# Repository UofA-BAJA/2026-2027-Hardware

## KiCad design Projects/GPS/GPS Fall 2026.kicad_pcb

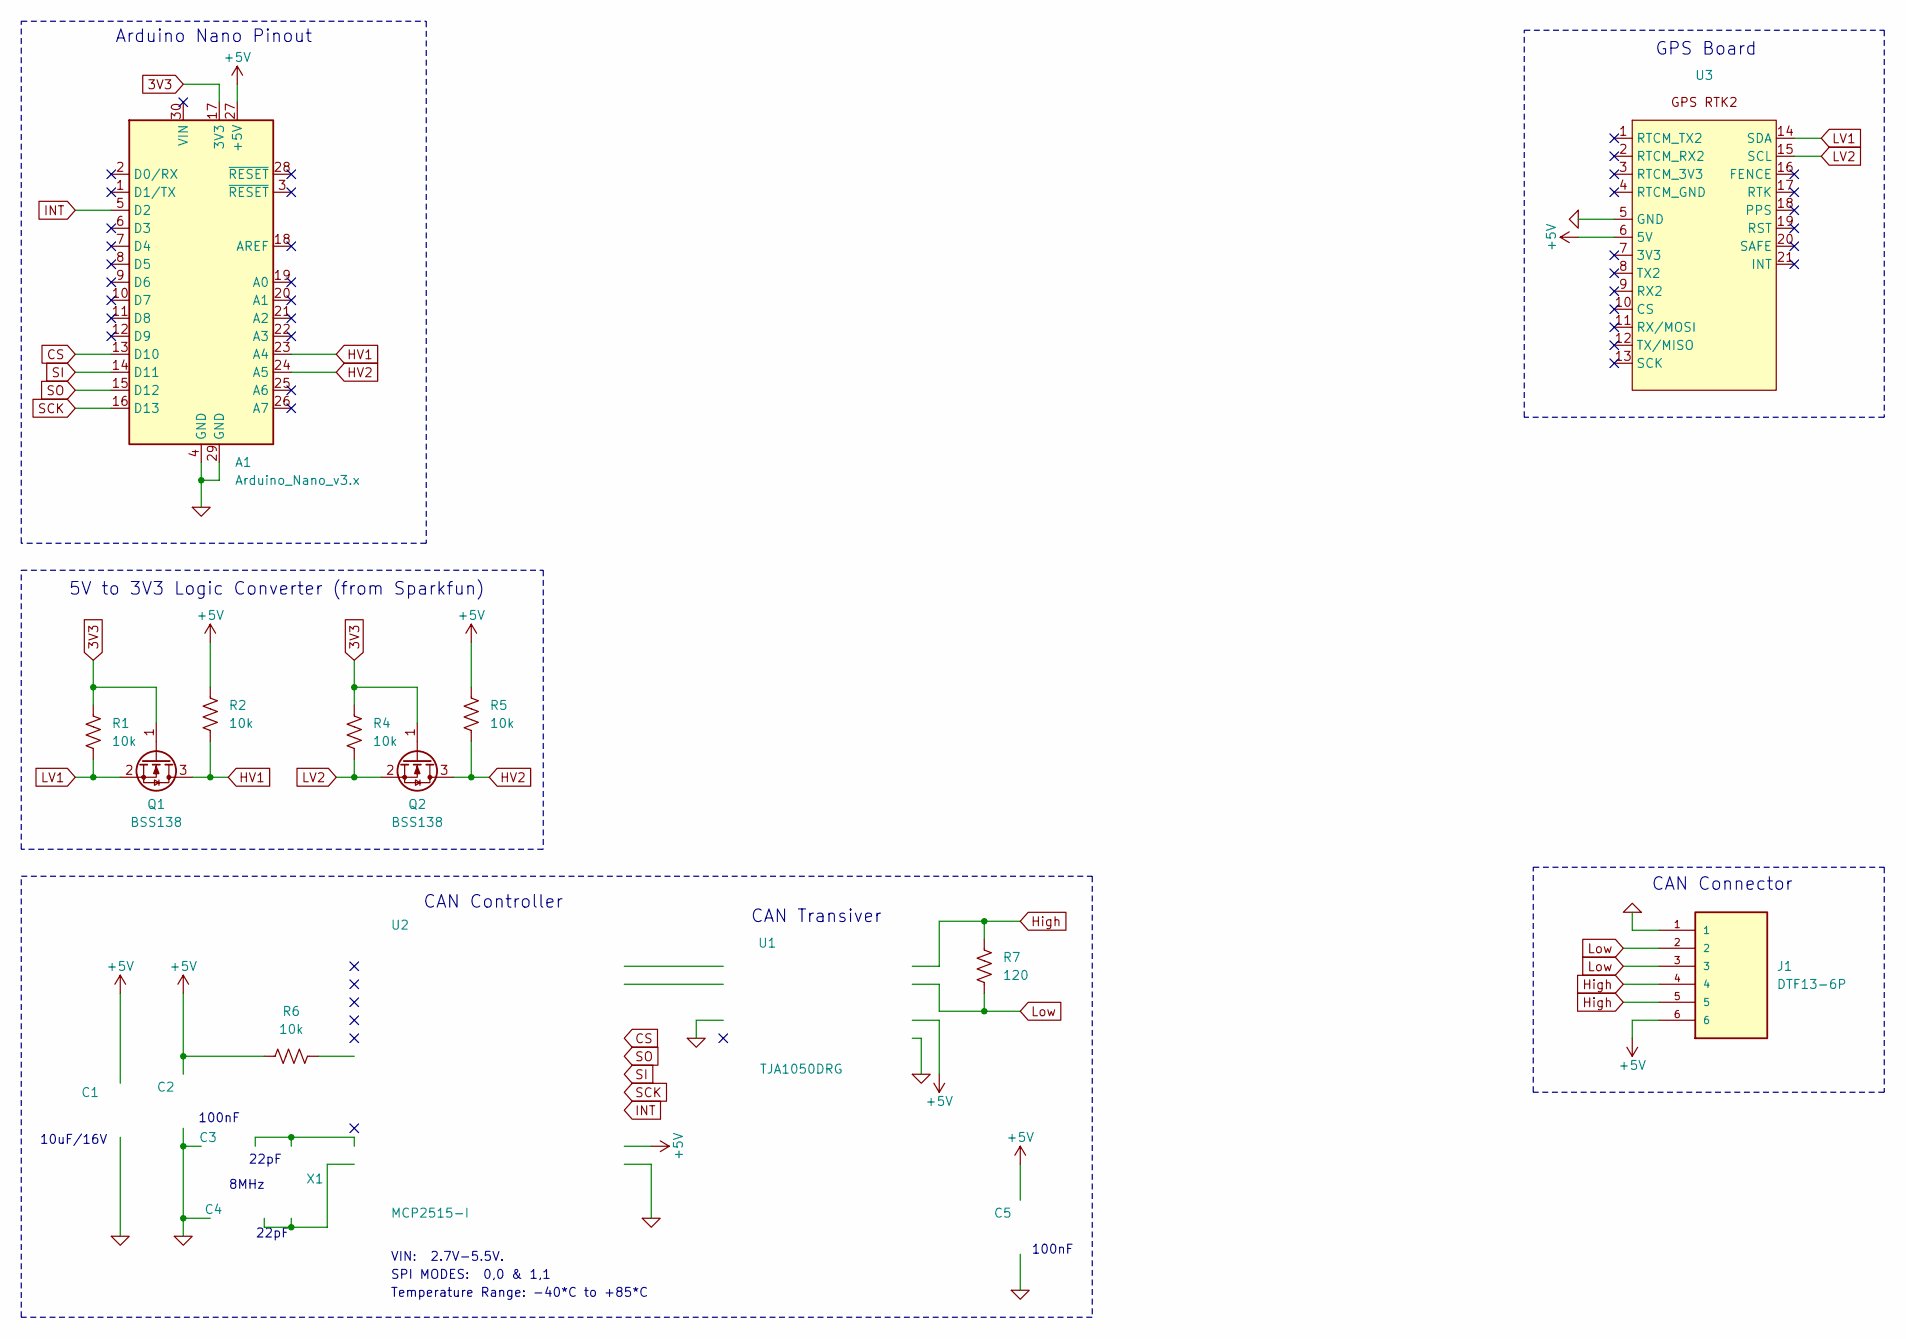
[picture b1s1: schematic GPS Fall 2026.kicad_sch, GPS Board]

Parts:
A1: Arduino_Nano_v3.x; Arduino_Nano
C1: 10uF/16V; CP_Radial_Tantal_D5.0mm_P2.50mm
C2, C5: 100nF; CP_Radial_D5.0mm_P2.50mm; PART NUMBER C0603-N.C.
C3, C4: 22pF; CP_Radial_D5.0mm_P2.50mm; PART NUMBER C0603-N.C.
J1: DTF13-6P; TE_DTF13-6P; PARTREV B
Q1, Q2: BSS138; SOT-23_Handsoldering
R1, R2, R4, R5, R6: 10k; R_Axial_DIN0207_L6.3mm_D2.5mm_P10.16mm_Horizontal
R7: 120; R_Axial_DIN0207_L6.3mm_D2.5mm_P10.16mm_Horizontal
U1: TJA1050DRG; SOIC-8_5.3x5.3mm_P1.27mm; MANUFACTURER PART TJA1050DRG; LCSC PART NAME TJA1050DRG
U2: MCP2515-I; SOIC-18W_7.5x11.6mm_P1.27mm; MANUFACTURER PART MCP2515-I; JLCPCB PART CLASS Extended Part
U3: GPS_RTK2
X1: 8MHz; Crystal_SMD_HC49-SD

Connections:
0: A1.4 (GND), A1.29 (GND), C1.2, C2.1, C3.2, C4.2, C5.1, J1.1, U1.2 (GND), U1.8 (STB), U2.9 (VSS), U3.5 (GND)
3V3: A1.17 (3V3), Q1.1 (G), Q2.1 (G), R1.1, R4.1
+5V: A1.27 (+5V), C1.1, C2.2, C5.2, J1.6, R2.1, R5.1, R6.1, U1.3 (VCC), U2.18 (VDD), U3.6 (5V)
CS: A1.13 (D10), U2.16 (~CS)
HV1: A1.23 (A4), Q1.3 (D), R2.2
HV2: A1.24 (A5), Q2.3 (D), R5.2
High: J1.4, J1.5, R7.1, U1.7 (CANH)
INT: A1.5 (D2), U2.12 (~INT)
LV1: Q1.2 (S), R1.2, U3.14 (SDA)
LV2: Q2.2 (S), R4.2, U3.15 (SCL)
Low: J1.2, J1.3, R7.2, U1.6 (CANL)
unnamed: U1.4 (RXD), U2.2 (RXCAN)
unnamed: U1.1 (TXD), U2.1 (TXCAN)
unnamed: C4.1, U2.8 (OSC1), X1.1
unnamed: C3.1, U2.7 (OSC2), X1.2
unnamed: R6.2, U2.17 (~RESET)
SCK: A1.16 (D13), U2.13 (SCK)
SI: A1.14 (D11), U2.14 (SI)
SO: A1.15 (D12), U2.15 (SO)

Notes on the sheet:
VIN: 2.7V-5.5V.
100nF
5V to 3V3 Logic Converter (from Sparkfun)
CAN Controller
CAN Connector
SPI MODES: 0,0 & 1,1
Arduino Nano Pinout
8MHz
GPS Board
CAN Transiver
22pF
Temperature Range: -40*C to +85*C
10uF/16V

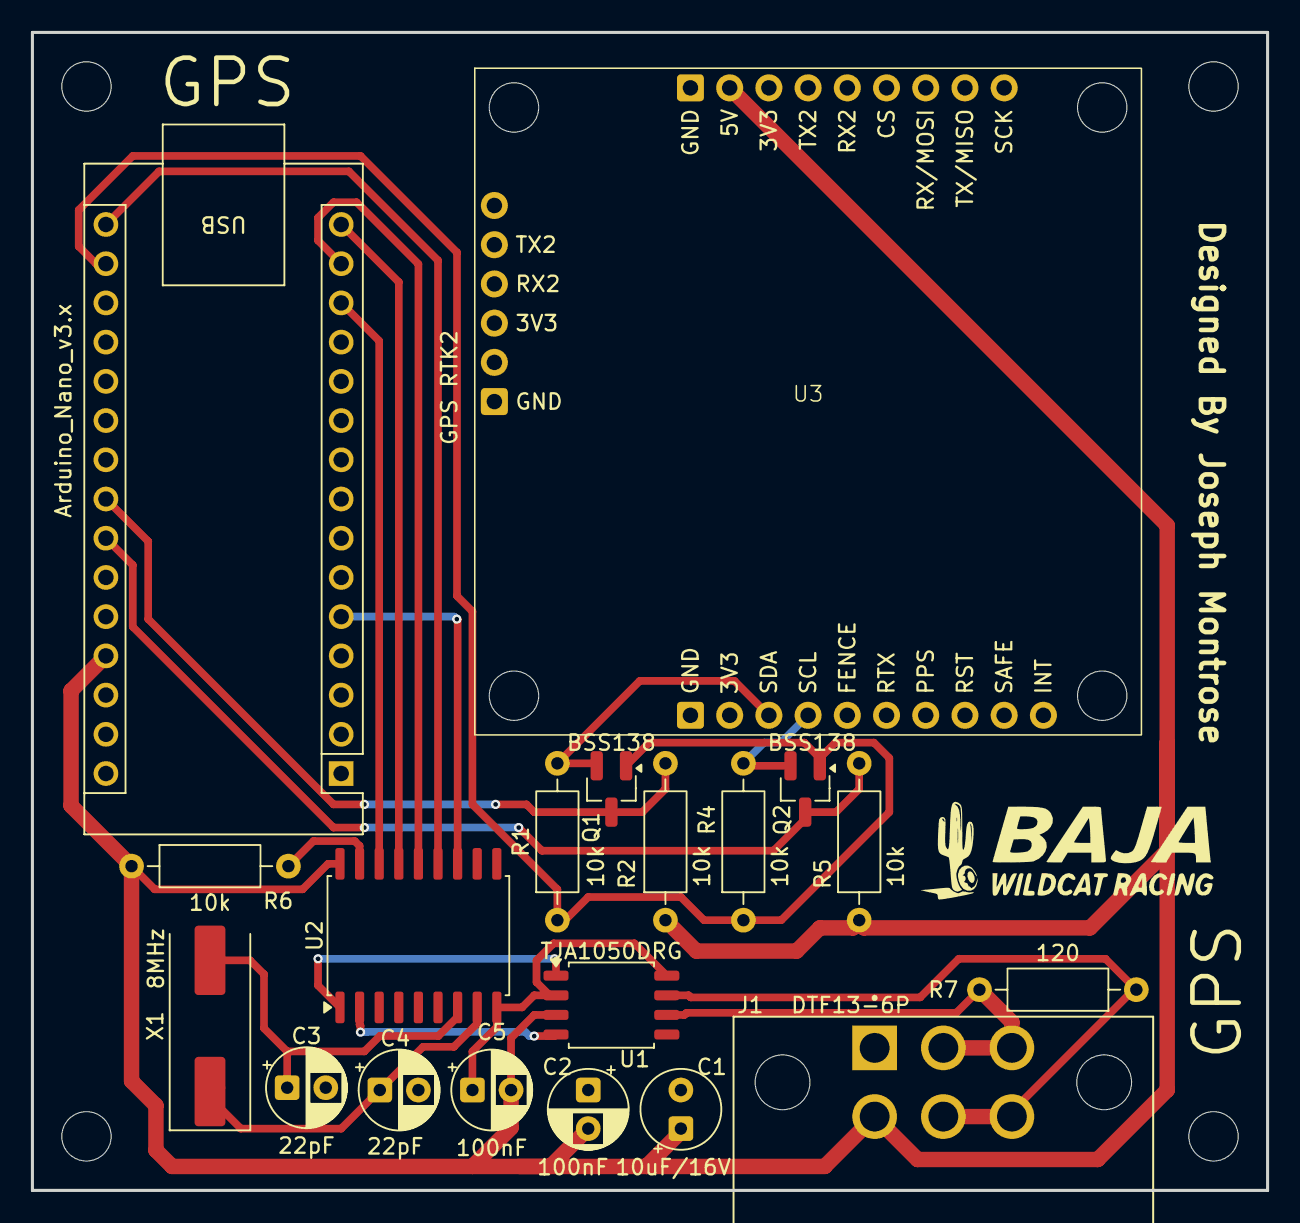
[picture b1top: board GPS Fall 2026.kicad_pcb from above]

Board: 2 copper layers, 80.0 x 75.0 mm, 19 parts (0 on the bottom side), 19 nets.
